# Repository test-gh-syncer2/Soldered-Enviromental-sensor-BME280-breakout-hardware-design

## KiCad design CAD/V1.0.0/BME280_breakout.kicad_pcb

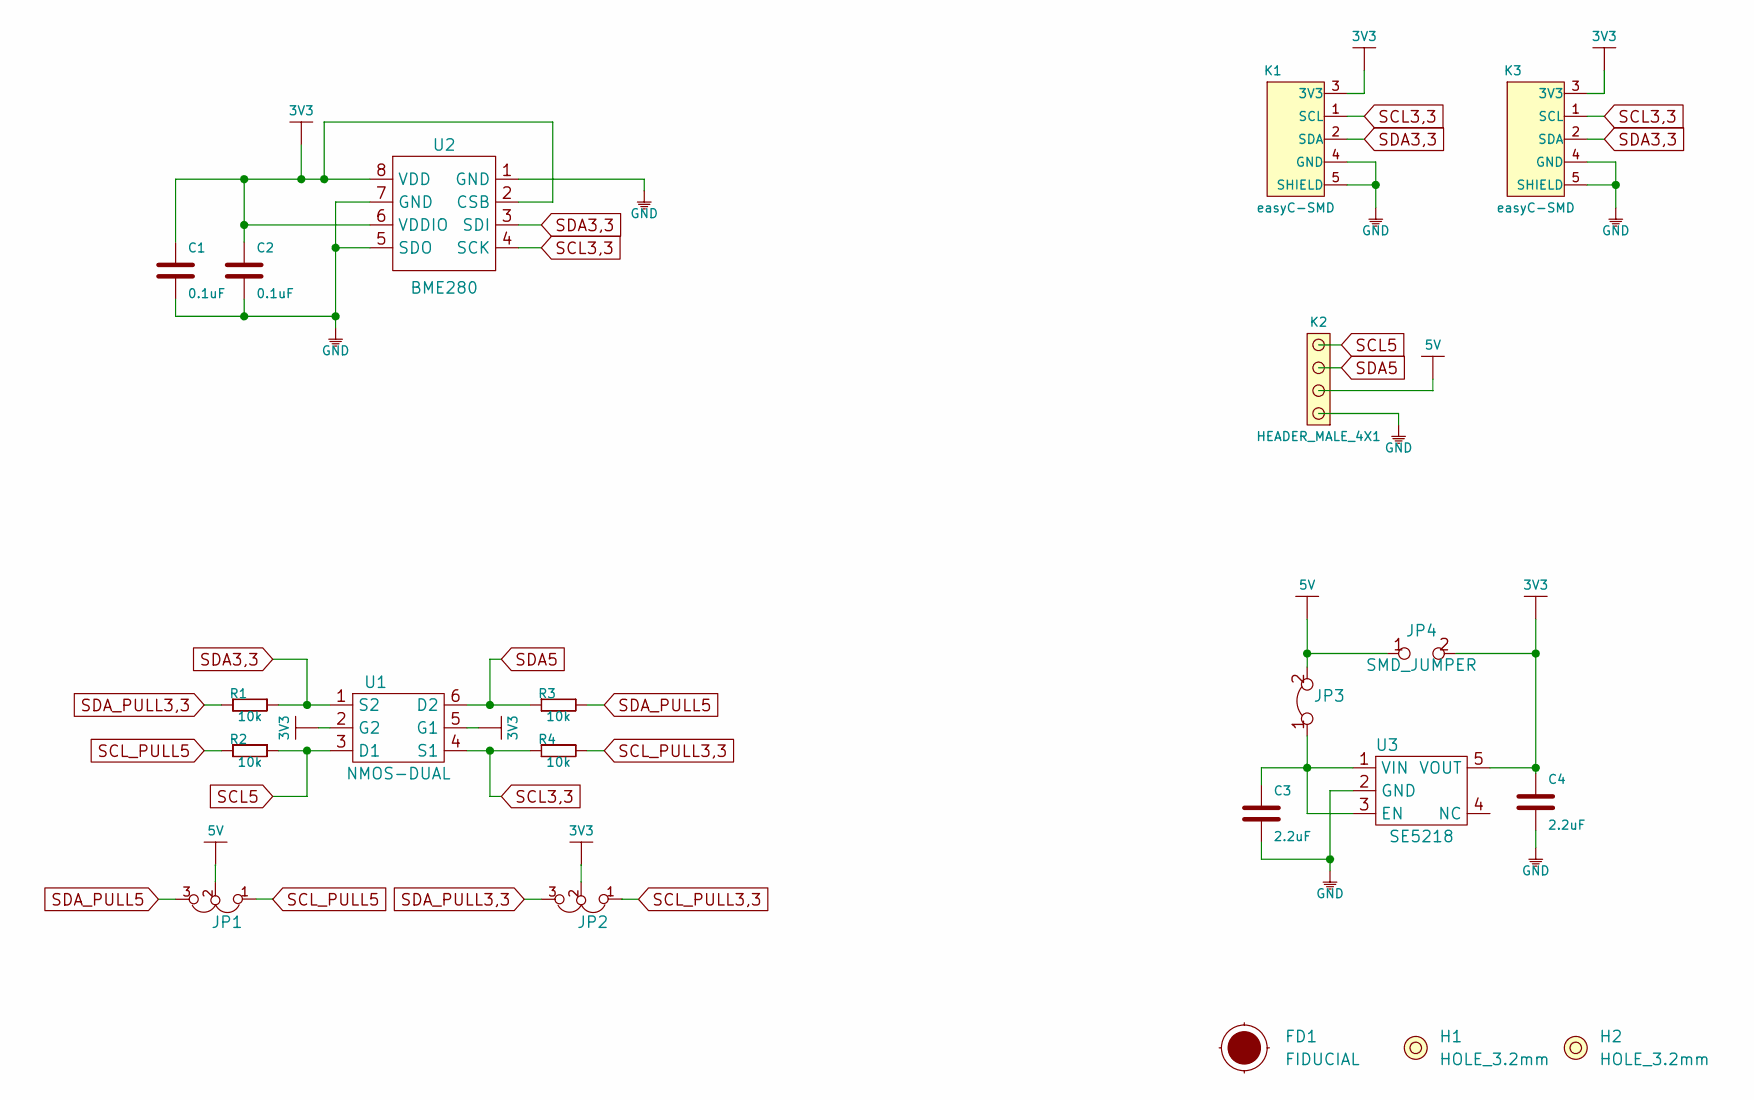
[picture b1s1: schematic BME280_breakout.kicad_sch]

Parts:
C1, C2: 0.1uF; 0603C
C3, C4: 2.2uF; 0603C
FD1: FIDUCIAL; FIDUCIAL_23
H1, H2: HOLE_3.2mm
JP1, JP2: SMD_JUMPER_3_PAD_TRACE
JP3: SMD-JUMPER-CONNECTED_TRACE_SLODERMASK
JP4: SMD_JUMPER
K1, K3: easyC-SMD; easyC-connector
K2: HEADER_MALE_4X1
R1, R2, R3, R4: 10k; 0603R
U1: NMOS-DUAL; SOT-363
U2: BME280
U3: SE5218; SOT-23-5

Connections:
3V3: C1.2, C2.2, C4.2, JP2.2, JP4.2, K1.3 (3V3), K3.3 (3V3), U1.2 (G2), U1.5 (G1), U2.2 (CSB), U2.6 (VDDIO), U2.8 (VDD), U3.5 (VOUT)
5V: JP1.2, JP3.2, JP4.1, K2.2
GND: C1.1, C2.1, C3.1, C4.1, K1.4 (GND), K1.5 (SHIELD), K2.1, K3.4 (GND), K3.5 (SHIELD), U2.1 (GND), U2.5 (SDO), U2.7 (GND), U3.2 (GND)
unnamed: C3.2, JP3.1, U3.1 (VIN), U3.3 (EN)
SCL3,3: K1.1 (SCL), K3.1 (SCL), R4.1, U1.4 (S1), U2.4 (SCK)
SCL5: K2.4, R2.2, U1.3 (D1)
SCL_PULL3,3: JP2.1, R4.2
SCL_PULL5: JP1.1, R2.1
SDA3,3: K1.2 (SDA), K3.2 (SDA), R1.2, U1.1 (S2), U2.3 (SDI)
SDA5: K2.3, R3.1, U1.6 (D2)
SDA_PULL3,3: JP2.3, R1.1
SDA_PULL5: JP1.3, R3.2

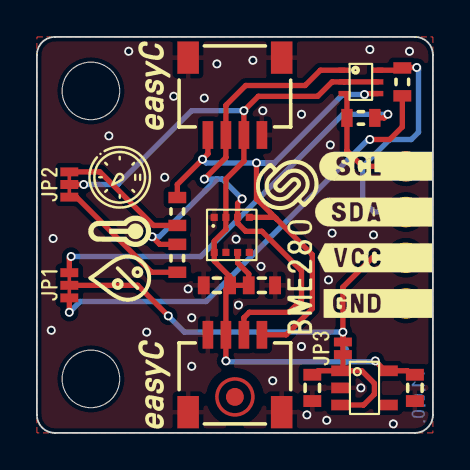
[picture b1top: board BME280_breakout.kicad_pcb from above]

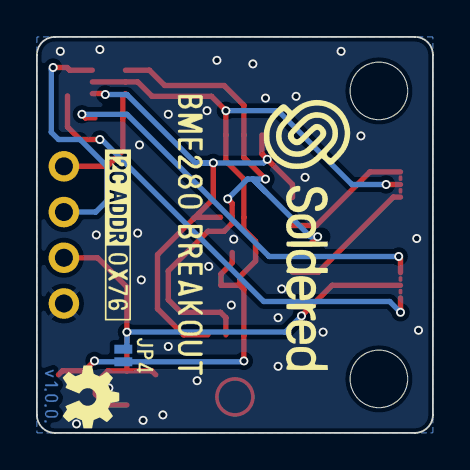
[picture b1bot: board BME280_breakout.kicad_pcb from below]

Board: 2 copper layers, 22.0 x 22.0 mm, 22 parts (3 on the bottom side), 12 nets.

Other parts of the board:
Ref**: Val**; Version1.0.0.

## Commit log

2021-09-23 Syncing to git
2021-09-23 Updating open source files.
